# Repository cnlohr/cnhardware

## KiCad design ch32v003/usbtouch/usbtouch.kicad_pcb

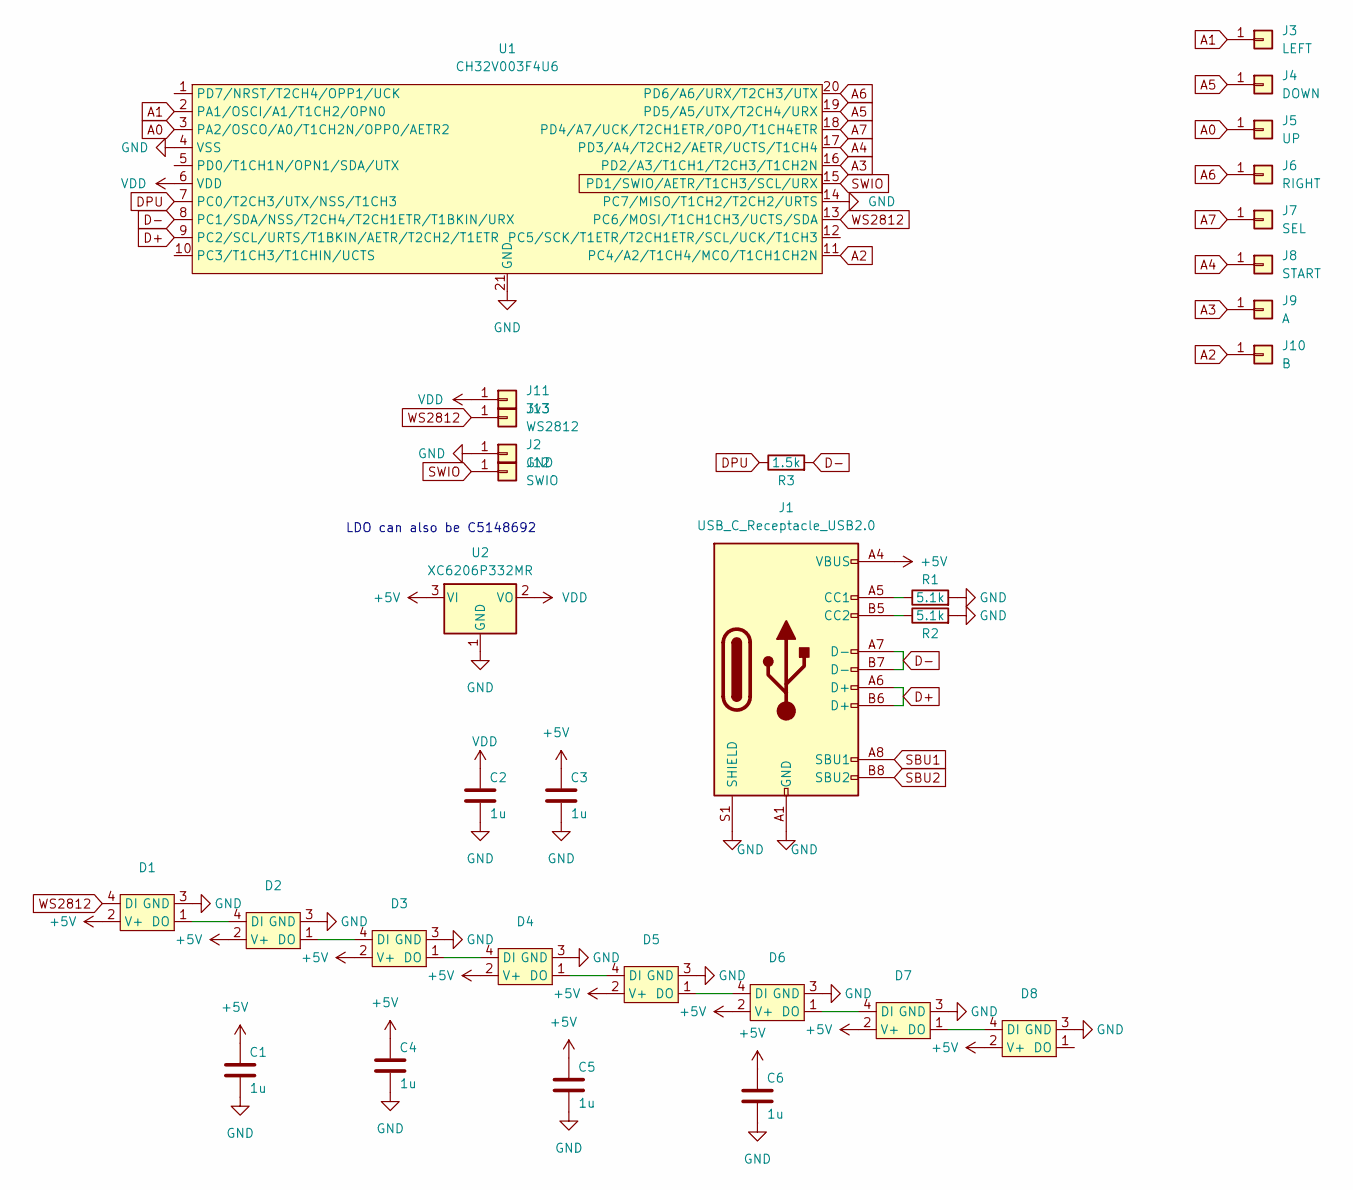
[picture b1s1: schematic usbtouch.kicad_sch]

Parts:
C1, C2, C3, C4, C5, C6: 1u; C_0603_1608Metric; LCSC C15849
D1, D2, D3, D4, D5, D6, D7, D8: XL-1615RGBC-WS2812B; LCSC C5349954
J1: USB_C_Receptacle_USB2.0; USB_C_PADDLE; LCSC C2765186
J2: GND; PinHeader_1x01_P2.54mm_Vertical
J3: LEFT; DPAD
J4: DOWN; DPAD
J5: UP; DPAD
J6: RIGHT; DPAD
J7: SEL; STARTSEL
J8: START; STARTSEL
J9: A; AB
J10: B; AB
J11: 3v3; PinHeader_1x01_P2.54mm_Vertical
J12: SWIO; PinHeader_1x01_P2.54mm_Vertical
J13: WS2812; PinHeader_1x01_P2.54mm_Vertical
R1, R2: 5.1k; R_0603_1608Metric; LCSC C23186
R3: 1.5k; R_0603_1608Metric; LCSC C22843
U1: CH32V003F4U6; QFN-20-1EP_3x3mm_P0.4mm_EP1.65x1.65mm; LCSC C5299908
U2: XC6206P332MR; SOT-23; LCSC C5446

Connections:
+5V: C1.2, C3.2, C4.2, C5.2, C6.2, D1.2 (V+), D2.2 (V+), D3.2 (V+), D4.2 (V+), D5.2 (V+), D6.2 (V+), D7.2 (V+), D8.2 (V+), J1.A4 (VBUS), J1.A9 (VBUS), J1.B4 (VBUS), J1.B9 (VBUS), U2.3 (VI)
A0: J5.1, U1.3 (PA2/OSCO/A0/T1CH2N/OPP0/AETR2)
A1: J3.1, U1.2 (PA1/OSCI/A1/T1CH2/OPN0)
A2: J10.1, U1.11 (PC4/A2/T1CH4/MCO/T1CH1CH2N)
A3: J9.1, U1.16 (PD2/A3/T1CH1/T2CH3/T1CH2N)
A4: J8.1, U1.17 (PD3/A4/T2CH2/AETR/UCTS/T1CH4)
A5: J4.1, U1.19 (PD5/A5/UTX/T2CH4/URX)
A6: J6.1, U1.20 (PD6/A6/URX/T2CH3/UTX)
A7: J7.1, U1.18 (PD4/A7/UCK/T2CH1ETR/OPO/T1CH4ETR)
D+: J1.A6 (D+), J1.B6 (D+), U1.9 (PC2/SCL/URTS/T1BKIN/AETR/T2CH2/T1ETR)
D-: J1.A7 (D-), J1.B7 (D-), R3.2, U1.8 (PC1/SDA/NSS/T2CH4/T2CH1ETR/T1BKIN/URX)
DPU: R3.1, U1.7 (PC0/T2CH3/UTX/NSS/T1CH3)
GND: C1.1, C2.1, C3.1, C4.1, C5.1, C6.1, D1.3 (GND), D2.3 (GND), D3.3 (GND), D4.3 (GND), D5.3 (GND), D6.3 (GND), D7.3 (GND), D8.3 (GND), J1.A1 (GND), J1.A12 (GND), J1.B1 (GND), J1.B12 (GND), J1.S1 (SHIELD), J2.1, R1.2, R2.2, U1.4 (VSS), U1.14 (PC7/MISO/T1CH2/T2CH2/URTS), U1.21 (GND), U2.1 (GND)
unnamed: D1.1 (DO), D2.4 (DI)
unnamed: D2.1 (DO), D3.4 (DI)
unnamed: D3.1 (DO), D4.4 (DI)
unnamed: D4.1 (DO), D5.4 (DI)
unnamed: D5.1 (DO), D6.4 (DI)
unnamed: D6.1 (DO), D7.4 (DI)
unnamed: D7.1 (DO), D8.4 (DI)
unnamed: J1.A5 (CC1), R1.1
unnamed: J1.B5 (CC2), R2.1
SBU1: J1.A8 (SBU1)
SBU2: J1.B8 (SBU2)
SWIO: J12.1, U1.15 (PD1/SWIO/AETR/T1CH3/SCL/URX)
VDD: C2.2, J11.1, U1.6 (VDD), U2.2 (VO)
WS2812: D1.4 (DI), J13.1, U1.13 (PC6/MOSI/T1CH1CH3/UCTS/SDA)

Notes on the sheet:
LDO can also be C5148692

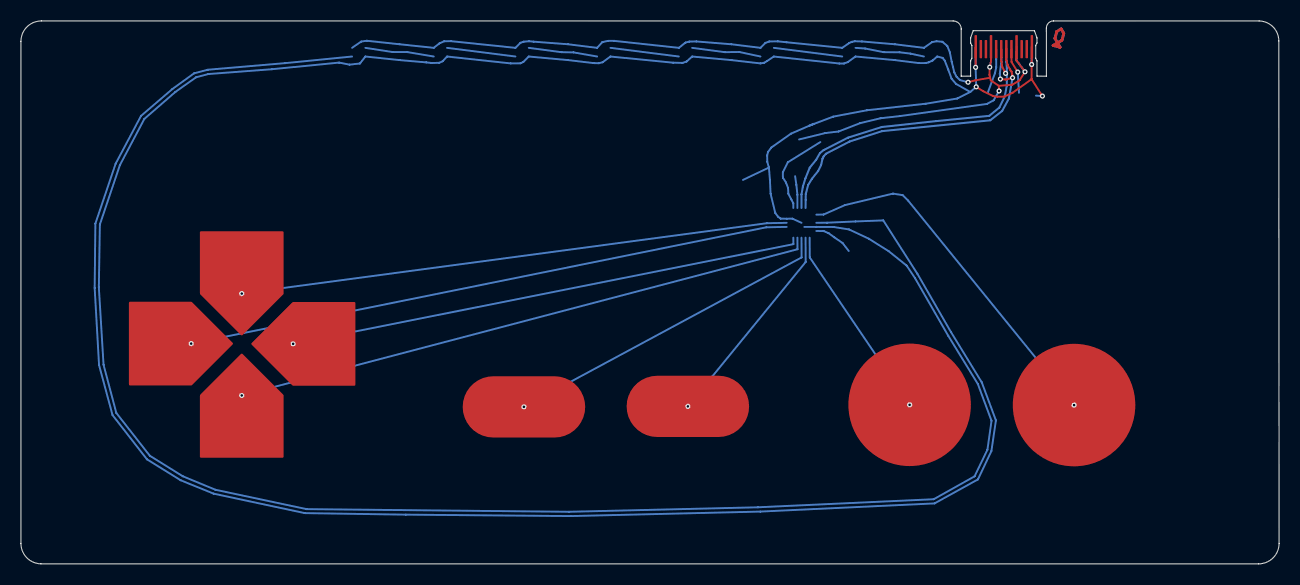
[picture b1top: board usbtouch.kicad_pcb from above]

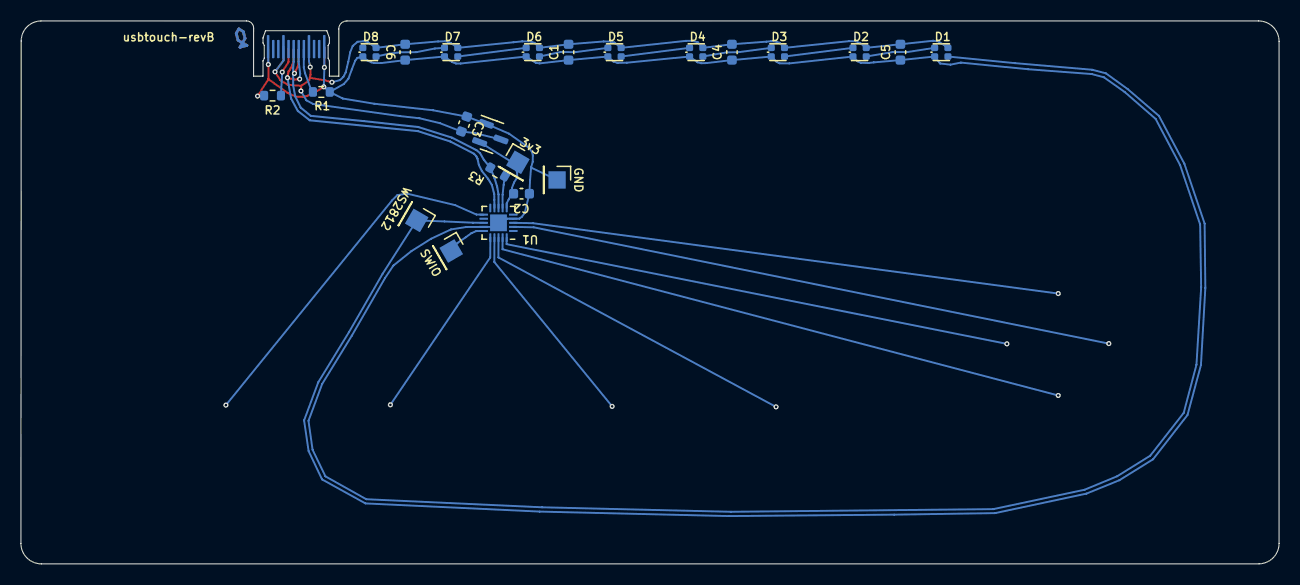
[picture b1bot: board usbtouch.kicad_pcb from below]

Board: 2 copper layers, 123.2 x 53.2 mm, 32 parts (24 on the bottom side), 25 nets.

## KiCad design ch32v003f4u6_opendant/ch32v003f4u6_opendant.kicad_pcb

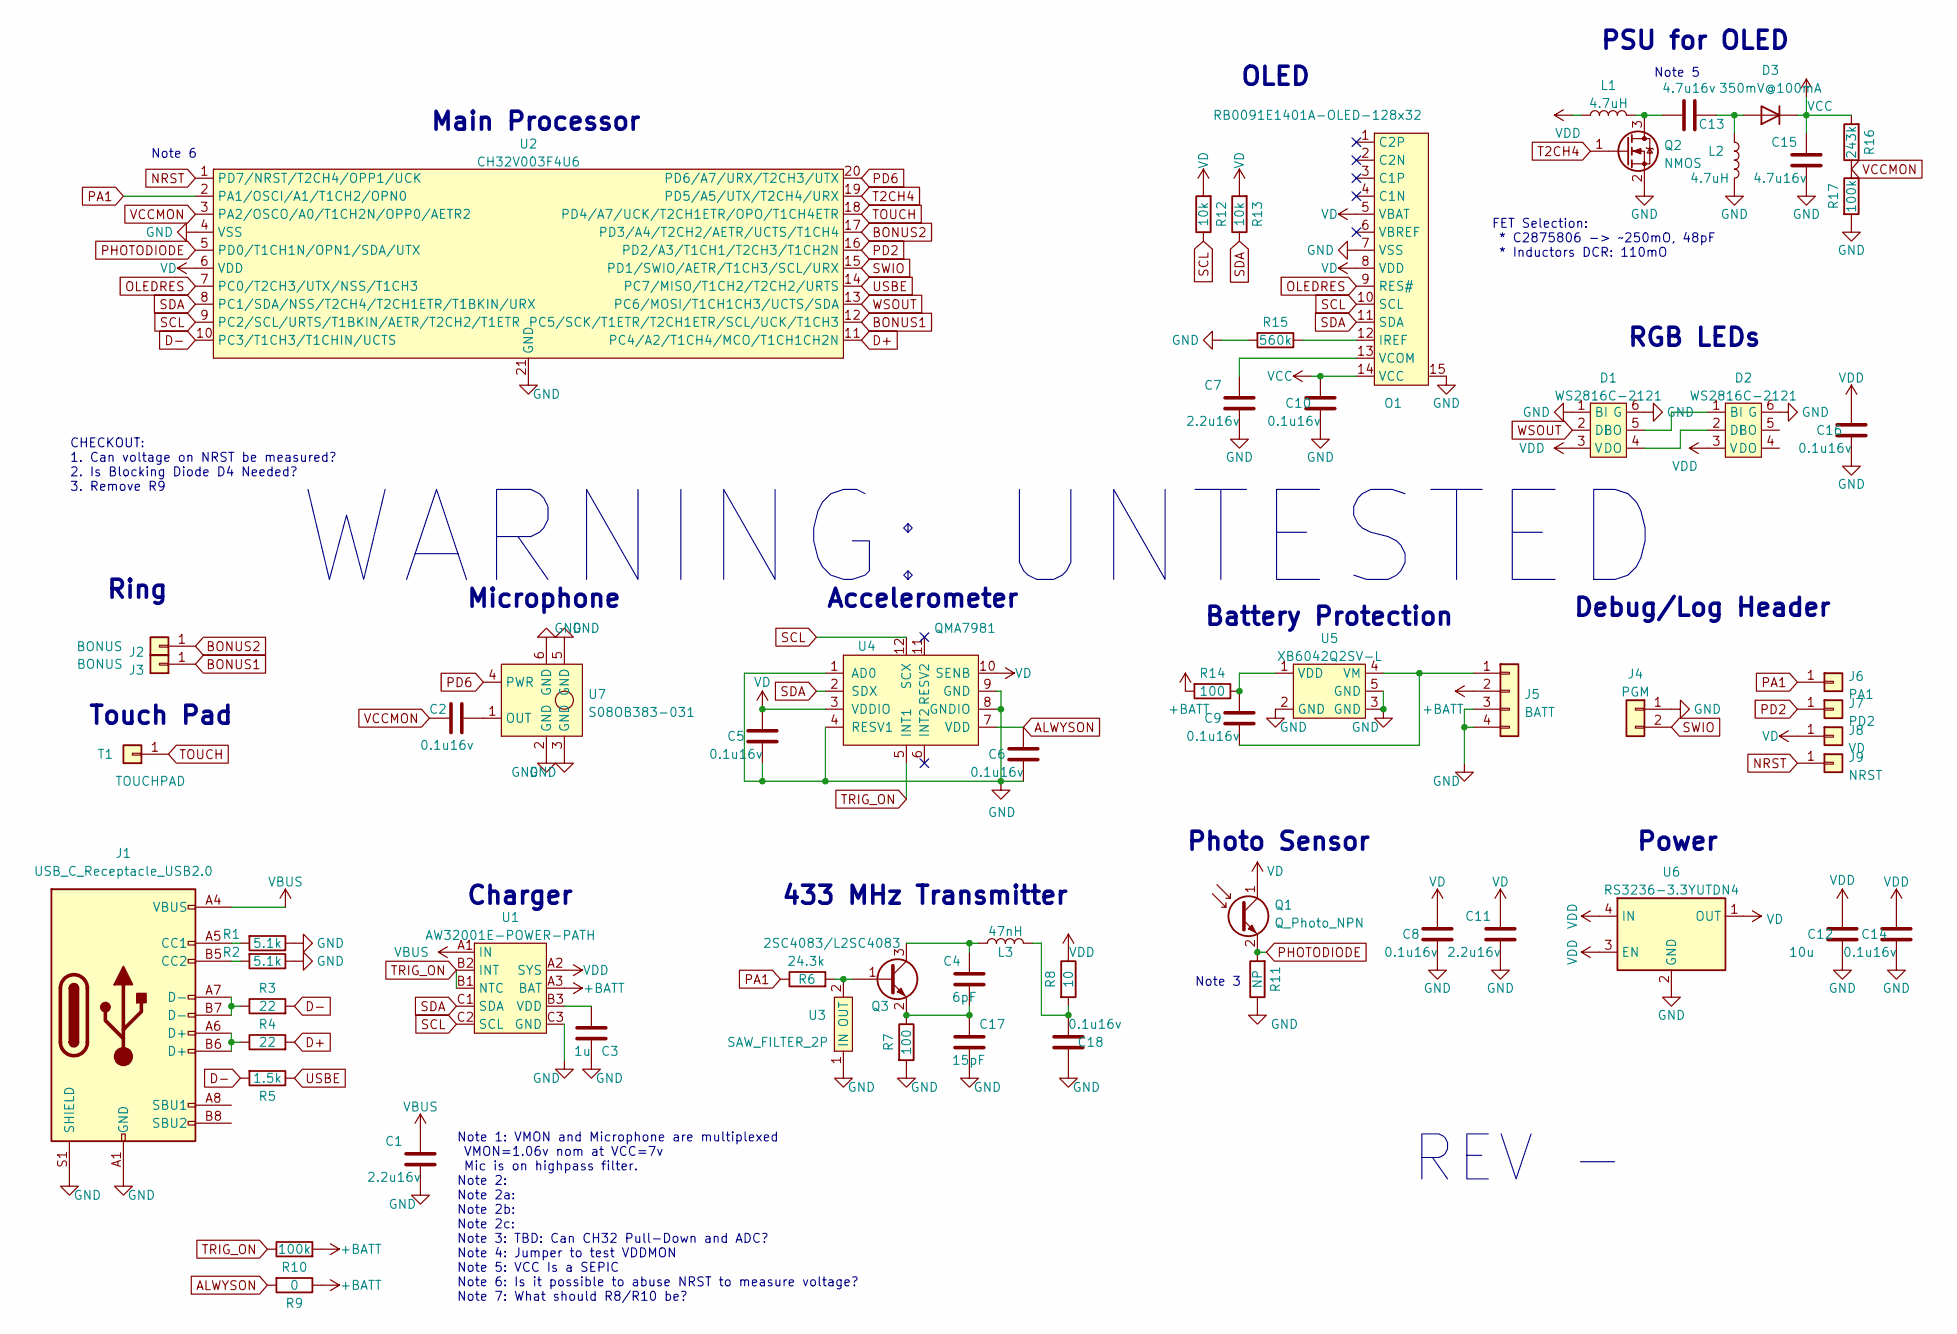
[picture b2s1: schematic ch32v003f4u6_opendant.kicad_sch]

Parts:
C1, C7, C11: 2.2u16v; C_0402_1005Metric; LCSC C385032
C2, C5, C6, C8, C9, C10, C14, C16, C18: 0.1u16v; C_0402_1005Metric; LCSC C338032
C3: 1u; C_0402_1005Metric; LCSC C52923
C4: 6pF; C_0402_1005Metric; LCSC C1575
C12: 10u; C_0402_1005Metric; LCSC C315248
C13, C15: 4.7u16v; C_0402_1005Metric; LCSC C412302
C17: 15pF; C_0402_1005Metric; LCSC C1548
D1, D2: WS2816C-2121; WS2816-2121; LCSC C965561
D3: 350mV@100mA; DFN1006; LCSC C239808
J1: USB_C_Receptacle_USB2.0; USB_C_Receptacle_HRO_TYPE-C-31-M-12; LCSC C2765186
J2, J3: BONUS; MountingHole_2.2mm_M2_DIN965_Pad
J4: PGM; PinHeader_1x02_P2.54mm_Vertical
J5: BATT; SOUHAN-Battery-1.25mm-SMT; LCSC C393945
J6: PA1; GeneralPad-Round-1.5mm
J7: PD2; GeneralPad-Round-1.5mm
J8: VD; GeneralPad-Round-1.5mm
J9: NRST; GeneralPad-Round-1.5mm
L1, L2: 4.7uH; L_0805_2012Metric; LCSC C379996
L3: 47nH; L_0603_1608Metric; LCSC C155023
O1: RB0091E1401A-OLED-128x32; RB0091E1401A-OLED-128x32_FLIP
Q1: Q_Photo_NPN; D_0805_2012Metric; LCSC C100090
Q2: NMOS; DFN-3L-1x0.6; LCSC C2875806
Q3: 2SC4083/L2SC4083; SOT-323_SC-70; LCSC C12064
R1, R2: 5.1k; R_0402_1005Metric; LCSC C114759
R3, R4: 22; R_0402_1005Metric; LCSC C102905
R5: 1.5k; R_0402_1005Metric; LCSC C114759
R6: 24.3k; R_0402_1005Metric; LCSC C226370
R7: 100; R_0402_1005Metric; LCSC C25076
R8: 10; R_0402_1005Metric; LCSC C140210
R9: 0; R_0402_1005Metric; LCSC C17168
R10, R17: 100k; R_0402_1005Metric; LCSC C279979
R11: NP; R_0402_1005Metric
R12, R13: 10k; R_0402_1005Metric; LCSC C269674
R14: 100; R_0402_1005Metric; LCSC C106232
R15: 560k; R_0402_1005Metric; LCSC C137958
R16: 243k; R_0402_1005Metric; LCSC C43249
T1: TOUCHPAD; touchpad_10x6.5mm_retircle
U1: AW32001E-POWER-PATH; BGA-9_1.6x1.6mm_Layout3x3_P0.5mm; LCSC C5125890
U2: CH32V003F4U6; QFN-20-1EP_3x3mm_P0.4mm_EP1.65x1.65mm; LCSC C5299908
U3: SAW_FILTER_2P; SAW-SMD2016-2P; LCSC C2847068
U4: QMA7981; QMA6981; LCSC C457290
U5: XB6042Q2SV-L; xdfn-reg; LCSC C2759995
U6: RS3236-3.3YUTDN4; xdfn-reg; LCSC C379350
U7: S08OB383-031; GOERTEK-S08OB383-031-MemsMic; LCSC S08OB383-031

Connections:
+BATT: J5.2, R9.1, R10.2, R14.2, U1.A3 (BAT)
ALWYSON: C6.1, R9.2, U4.7 (VDD)
BONUS1: J3.1, U2.12 (PC5/SCK/T1ETR/T2CH1ETR/SCL/UCK/T1CH3)
BONUS2: J2.1, U2.17 (PD3/A4/T2CH2/AETR/UCTS/T1CH4)
D+: R4.2, U2.11 (PC4/A2/T1CH4/MCO/T1CH1CH2N)
D-: R3.2, R5.2, U2.10 (PC3/T1CH3/T1CHIN/UCTS)
GND: C1.2, C3.2, C5.2, C6.2, C7.2, C8.2, C10.2, C11.2, C12.2, C14.2, C15.2, C16.2, C17.2, C18.1, D1.1 (BI), D1.6 (G), D2.6 (G), J1.A1 (GND), J1.A12 (GND), J1.B1 (GND), J1.B12 (GND), J1.S1 (SHIELD), J4.1, J5.3, J5.4, L2.2, O1.7 (VSS), O1.15, Q2.2 (S), R1.1, R2.1, R7.2, R11.1, R15.2, R17.2, U1.C3 (GND), U2.4 (VSS), U2.21 (GND), U3.1 (IN), U4.1 (AD0), U4.4 (RESV1), U4.8 (GNDIO), U4.9 (GND), U5.2 (GND), U5.3 (GND), U5.5 (GND), U6.2 (GND), U6.5 (GND), U7.2 (GND), U7.3 (GND), U7.5 (GND), U7.6 (GND)
NRST: J9.1, U2.1 (PD7/NRST/T2CH4/OPP1/UCK)
unnamed: C2.2, U7.1 (OUT)
unnamed: C3.1, U1.B3 (VDD)
unnamed: C4.1, L3.1, Q3.3 (C)
unnamed: C7.1, O1.13 (VCOM)
unnamed: C9.1, R14.1, U5.1 (VDD)
unnamed: C9.2, J5.1, U5.4 (VM)
unnamed: C13.1, L1.2, Q2.3 (D)
unnamed: C13.2, D3.2 (A), L2.1
unnamed: C4.2, C17.1, Q3.2 (E), R7.1
unnamed: C18.2, L3.2, R8.2
unnamed: D1.4 (DO), D2.2 (DI)
unnamed: D1.5 (BO), D2.1 (BI)
unnamed: J1.A5 (CC1), R1.2
unnamed: J1.A6 (D+), J1.B6 (D+), R4.1
unnamed: J1.A7 (D-), J1.B7 (D-), R3.1
unnamed: J1.B5 (CC2), R2.2
unnamed: O1.12 (IREF), R15.1
unnamed: Q3.1 (B), R6.2, U3.2 (OUT)
OLEDRES: O1.9 (RES#), U2.7 (PC0/T2CH3/UTX/NSS/T1CH3)
PA1: J6.1, R6.1, U2.2 (PA1/OSCI/A1/T1CH2/OPN0)
PD2: J7.1, U2.16 (PD2/A3/T1CH1/T2CH3/T1CH2N)
PD6: U2.20 (PD6/A7/URX/T2CH3/UTX), U7.4 (PWR)
PHOTODIODE: Q1.2 (E), R11.2, U2.5 (PD0/T1CH1N/OPN1/SDA/UTX)
SCL: O1.10 (SCL), R12.1, U1.C2 (SCL), U2.9 (PC2/SCL/URTS/T1BKIN/AETR/T2CH2/T1ETR), U4.12 (SCX)
SDA: O1.11 (SDA), R13.1, U1.C1 (SDA), U2.8 (PC1/SDA/NSS/T2CH4/T2CH1ETR/T1BKIN/URX), U4.2 (SDX)
SWIO: J4.2, U2.15 (PD1/SWIO/AETR/T1CH3/SCL/URX)
T2CH4: Q2.1 (G), U2.19 (PD5/A5/UTX/T2CH4/URX)
TOUCH: T1.1, U2.18 (PD4/A7/UCK/T2CH1ETR/OPO/T1CH4ETR)
TRIG_ON: R10.1, U1.B1 (NTC), U1.B2 (INT), U4.5 (INT1)
USBE: R5.1, U2.14 (PC7/MISO/T1CH2/T2CH2/URTS)
VBUS: C1.1, J1.A4 (VBUS), J1.A9 (VBUS), J1.B4 (VBUS), J1.B9 (VBUS), U1.A1 (IN)
VCC: C10.1, C15.1, D3.1 (K), O1.14 (VCC), R16.2
VCCMON: C2.1, R16.1, R17.1, U2.3 (PA2/OSCO/A0/T1CH2N/OPP0/AETR2)
VD: C5.1, C8.1, C11.1, J8.1, O1.5 (VBAT), O1.8 (VDD), Q1.1 (C), R12.2, R13.2, U2.6 (VDD), U4.3 (VDDIO), U4.10 (SENB), U6.1 (OUT)
VDD: C12.1, C14.1, C16.1, D1.3 (V), D2.3 (V), L1.1, R8.1, U1.A2 (SYS), U6.3 (EN), U6.4 (IN)
WSOUT: D1.2 (DI), U2.13 (PC6/MOSI/T1CH1CH3/UCTS/SDA)

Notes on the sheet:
Accelerometer
Note 5
REV -
Ring
Microphone
Note 3
WARNING: UNTESTED
433 MHz Transmitter
RGB LEDs
Battery Protection
PSU for OLED
Debug/Log Header
OLED
FET Selection: * C2875806 -> ~250mO, 48pF * Inductors DCR: 110mO
Main Processor
Power
Charger
Photo Sensor
Note 6
CHECKOUT: 1. Can voltage on NRST be measured? 2. Is Blocking Diode D4 Needed? 3. Remove R9
Note 1: VMON and Microphone are multiplexed VMON=1.06v nom at VCC=7v Mic is on highpass filter. Note 2: Note 2a: Note 2b: Note 2c: Note 3: TBD: Can CH32 Pull-Down and ADC? Note 4: Jumper to test VDDMON Note 5: VCC Is a SEPIC Note 6: Is it possible to abuse NRST to measure voltage? Note 7: What shou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
Touch Pad

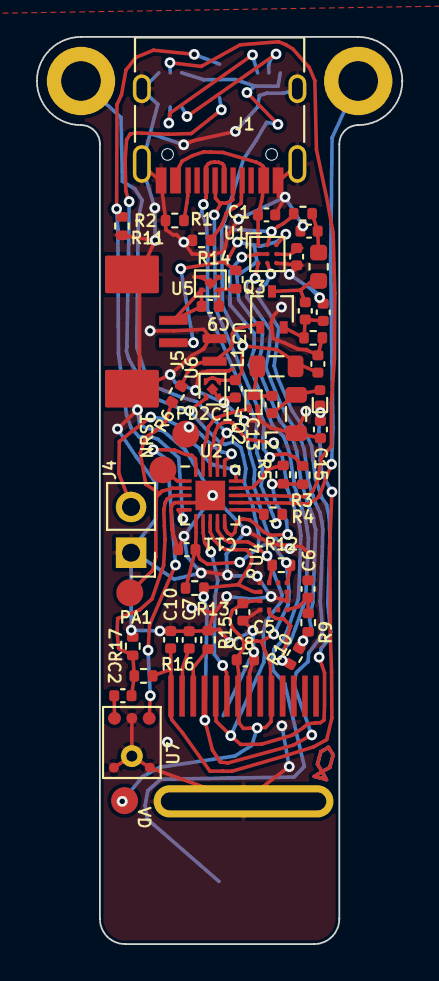
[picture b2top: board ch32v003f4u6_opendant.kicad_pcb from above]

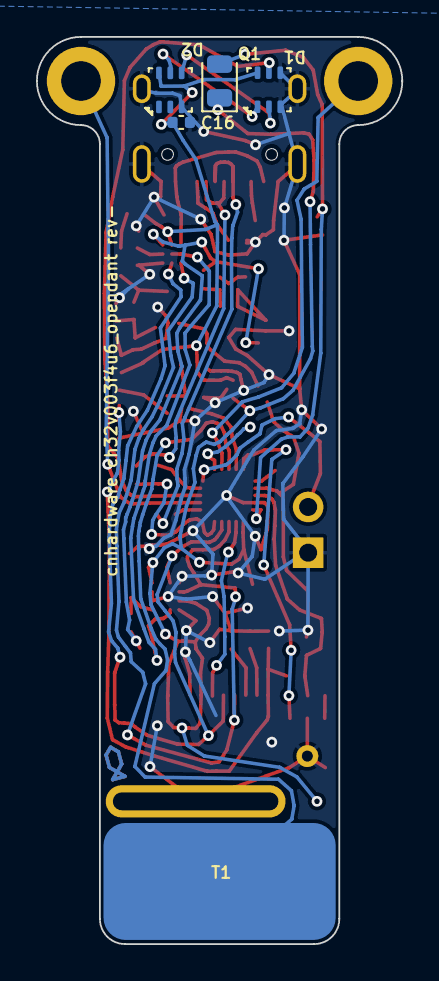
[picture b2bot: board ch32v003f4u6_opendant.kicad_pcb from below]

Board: 2 copper layers, 20.3 x 50.4 mm, 62 parts (5 on the bottom side), 44 nets.

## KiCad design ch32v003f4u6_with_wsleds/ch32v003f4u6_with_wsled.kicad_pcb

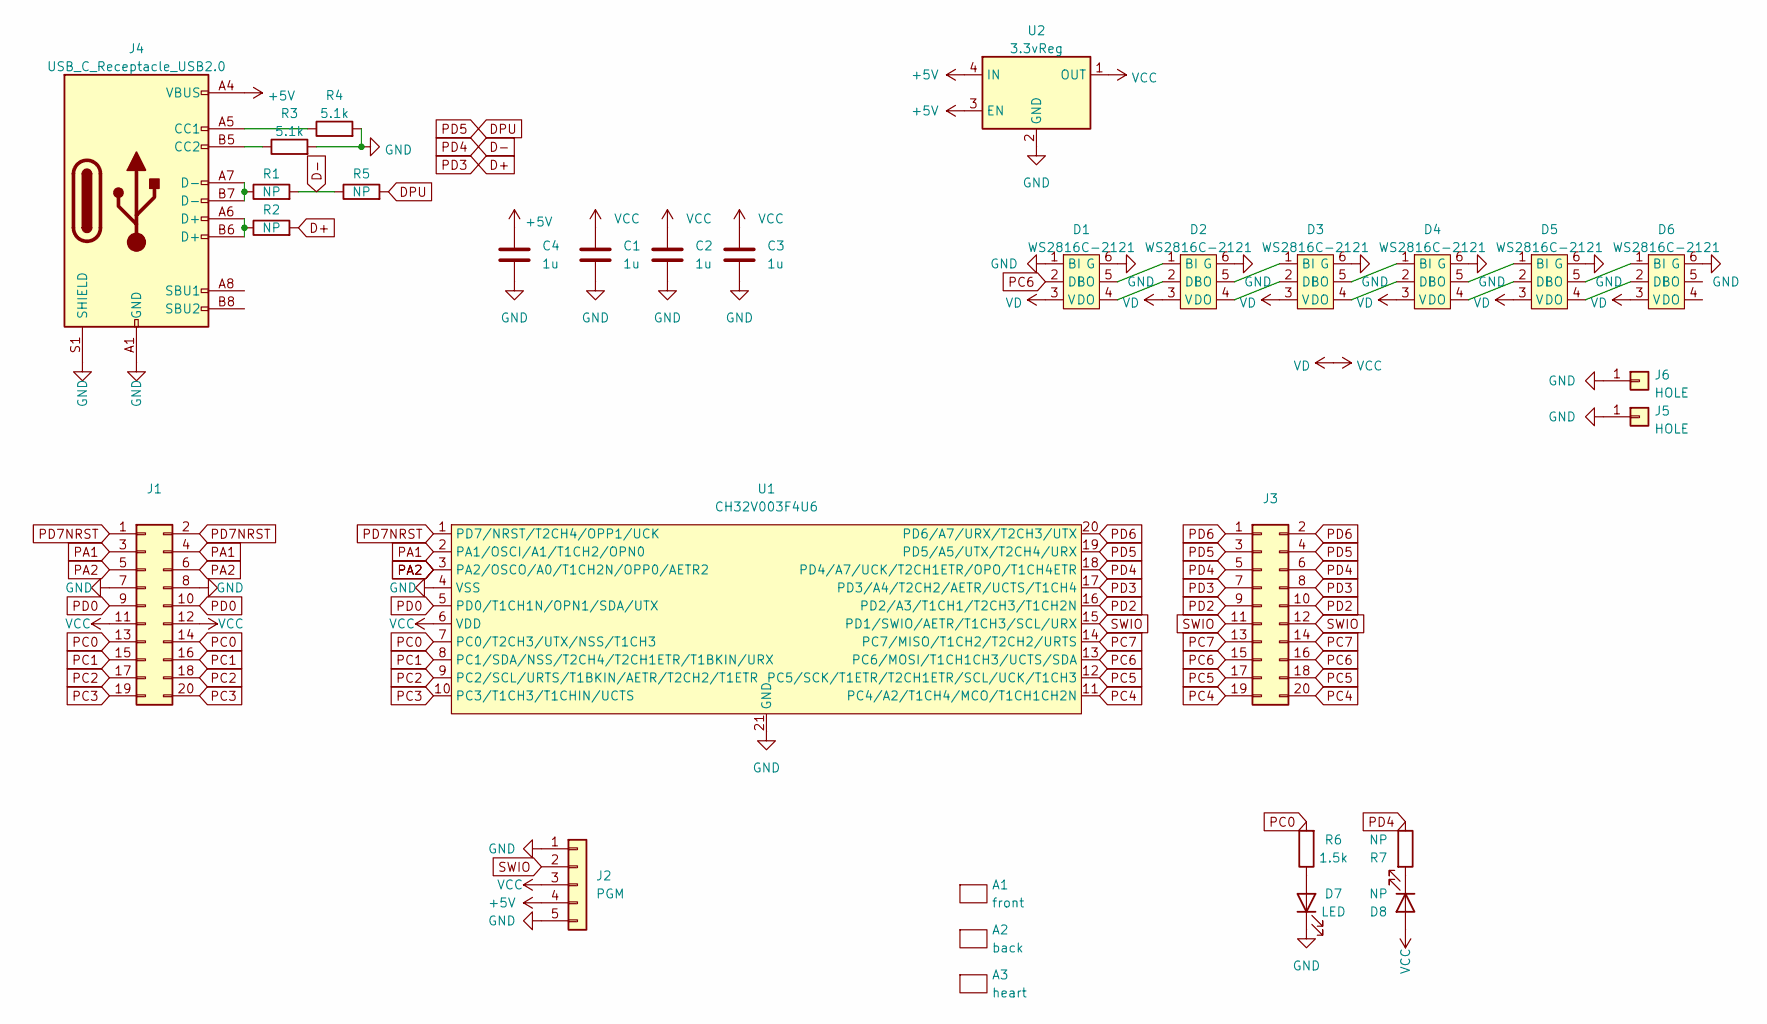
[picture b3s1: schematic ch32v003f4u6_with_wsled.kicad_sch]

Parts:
A1: front; Front
A2: back; Back
A3: heart; Heart
C1, C2, C3, C4: 1u; C_0402_1005Metric; LCSC C237173
D1, D2, D3, D4, D5, D6: WS2816C-2121; WS2816-2121; LCSC C965561
D7: LED; LED_0402_1005Metric; LCSC C74342
D8: NP; LED_0402_1005Metric; LCSC NP
J1, J3: PinHeader_2x10_P2.54mm_Vertical; LCSC C124359
J2: PGM; PinHeader_1x05_P2.54mm_Vertical; LCSC C358687
J4: USB_C_Receptacle_USB2.0; USB_C_Receptacle_HRO_TYPE-C-31-M-12; LCSC C709358
J5, J6: HOLE; MountingHole_2.2mm_M2_DIN965_Pad
R1, R2, R5: NP; R_0402_1005Metric
R3, R4: 5.1k; R_0402_1005Metric; LCSC C258132
R6: 1.5k; R_0402_1005Metric; LCSC C25867
R7: NP; R_0402_1005Metric; LCSC NP
U1: CH32V003F4U6; QFN-20-1EP_3x3mm_P0.4mm_EP1.65x1.65mm; LCSC C5299908
U2: 3.3vReg; xdfn-reg; LCSC C81114

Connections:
+5V: C4.1, J2.4, J4.A4 (VBUS), J4.A9 (VBUS), J4.B4 (VBUS), J4.B9 (VBUS), U2.3 (EN), U2.4 (IN)
D+: J3.7, J3.8, R2.2, U1.17 (PD3/A4/T2CH2/AETR/UCTS/T1CH4)
D-: J3.5, J3.6, R1.2, R5.1, R7.1, U1.18 (PD4/A7/UCK/T2CH1ETR/OPO/T1CH4ETR)
DPU: J3.3, J3.4, R5.2, U1.19 (PD5/A5/UTX/T2CH4/URX)
GND: C1.2, C2.2, C3.2, C4.2, D1.1 (BI), D1.6 (G), D2.6 (G), D3.6 (G), D4.6 (G), D5.6 (G), D6.6 (G), D7.1 (K), J1.7, J1.8, J2.1, J2.5, J4.A1 (GND), J4.A12 (GND), J4.B1 (GND), J4.B12 (GND), J4.S1 (SHIELD), J5.1, J6.1, R3.2, R4.2, U1.4 (VSS), U1.21 (GND), U2.2 (GND), U2.5 (GND)
unnamed: D1.4 (DO), D2.2 (DI)
unnamed: D1.5 (BO), D2.1 (BI)
unnamed: D2.4 (DO), D3.2 (DI)
unnamed: D2.5 (BO), D3.1 (BI)
unnamed: D3.4 (DO), D4.2 (DI)
unnamed: D3.5 (BO), D4.1 (BI)
unnamed: D4.4 (DO), D5.2 (DI)
unnamed: D4.5 (BO), D5.1 (BI)
unnamed: D5.4 (DO), D6.2 (DI)
unnamed: D5.5 (BO), D6.1 (BI)
unnamed: D7.2 (A), R6.1
unnamed: D8.1 (K), R7.2
unnamed: J4.A5 (CC1), R4.1
unnamed: J4.A6 (D+), J4.B6 (D+), R2.1
unnamed: J4.A7 (D-), J4.B7 (D-), R1.1
unnamed: J4.B5 (CC2), R3.1
PA1: J1.3, J1.4, U1.2 (PA1/OSCI/A1/T1CH2/OPN0)
PA2: J1.5, J1.6, U1.3 (PA2/OSCO/A0/T1CH2N/OPP0/AETR2)
PC0: J1.13, J1.14, R6.2, U1.7 (PC0/T2CH3/UTX/NSS/T1CH3)
PC1: J1.15, J1.16, U1.8 (PC1/SDA/NSS/T2CH4/T2CH1ETR/T1BKIN/URX)
PC2: J1.17, J1.18, U1.9 (PC2/SCL/URTS/T1BKIN/AETR/T2CH2/T1ETR)
PC3: J1.19, J1.20, U1.10 (PC3/T1CH3/T1CHIN/UCTS)
PC4: J3.19, J3.20, U1.11 (PC4/A2/T1CH4/MCO/T1CH1CH2N)
PC5: J3.17, J3.18, U1.12 (PC5/SCK/T1ETR/T2CH1ETR/SCL/UCK/T1CH3)
PC6: D1.2 (DI), J3.15, J3.16, U1.13 (PC6/MOSI/T1CH1CH3/UCTS/SDA)
PC7: J3.13, J3.14, U1.14 (PC7/MISO/T1CH2/T2CH2/URTS)
PD0: J1.9, J1.10, U1.5 (PD0/T1CH1N/OPN1/SDA/UTX)
PD2: J3.9, J3.10, U1.16 (PD2/A3/T1CH1/T2CH3/T1CH2N)
PD6: J3.1, J3.2, U1.20 (PD6/A7/URX/T2CH3/UTX)
PD7NRST: J1.1, J1.2, U1.1 (PD7/NRST/T2CH4/OPP1/UCK)
SWIO: J2.2, J3.11, J3.12, U1.15 (PD1/SWIO/AETR/T1CH3/SCL/URX)
VCC: C1.1, C2.1, C3.1, D1.3 (V), D2.3 (V), D3.3 (V), D4.3 (V), D5.3 (V), D6.3 (V), D8.2 (A), J1.11, J1.12, J2.3, U1.6 (VDD), U2.1 (OUT)

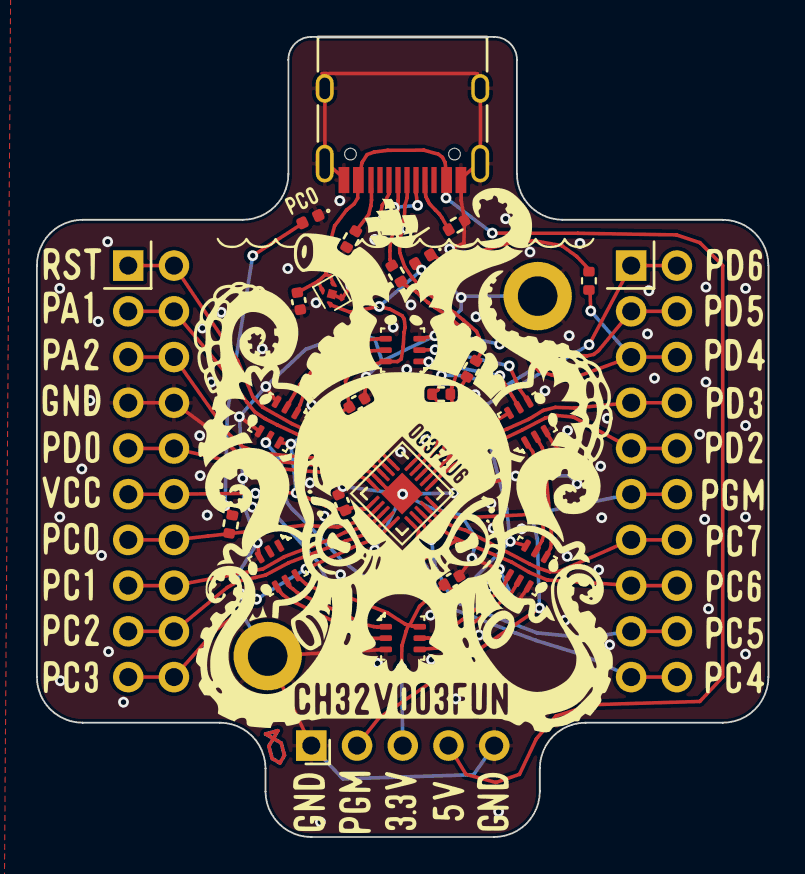
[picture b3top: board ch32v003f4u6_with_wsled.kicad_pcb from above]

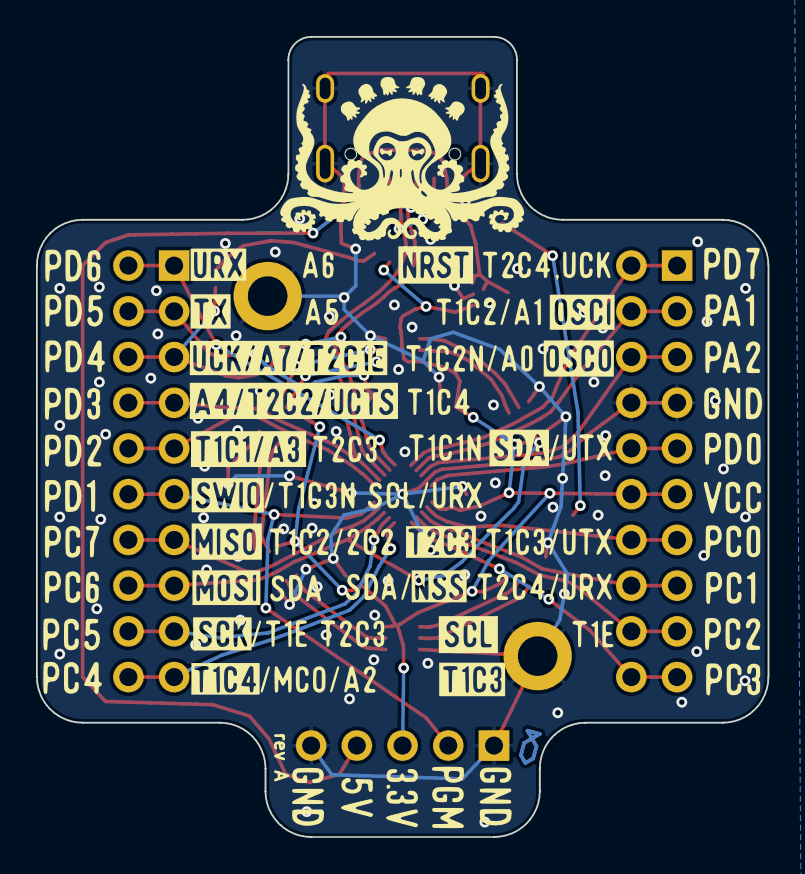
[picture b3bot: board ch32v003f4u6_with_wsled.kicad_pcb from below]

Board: 2 copper layers, 40.6 x 44.5 mm, 30 parts (2 on the bottom side), 37 nets.

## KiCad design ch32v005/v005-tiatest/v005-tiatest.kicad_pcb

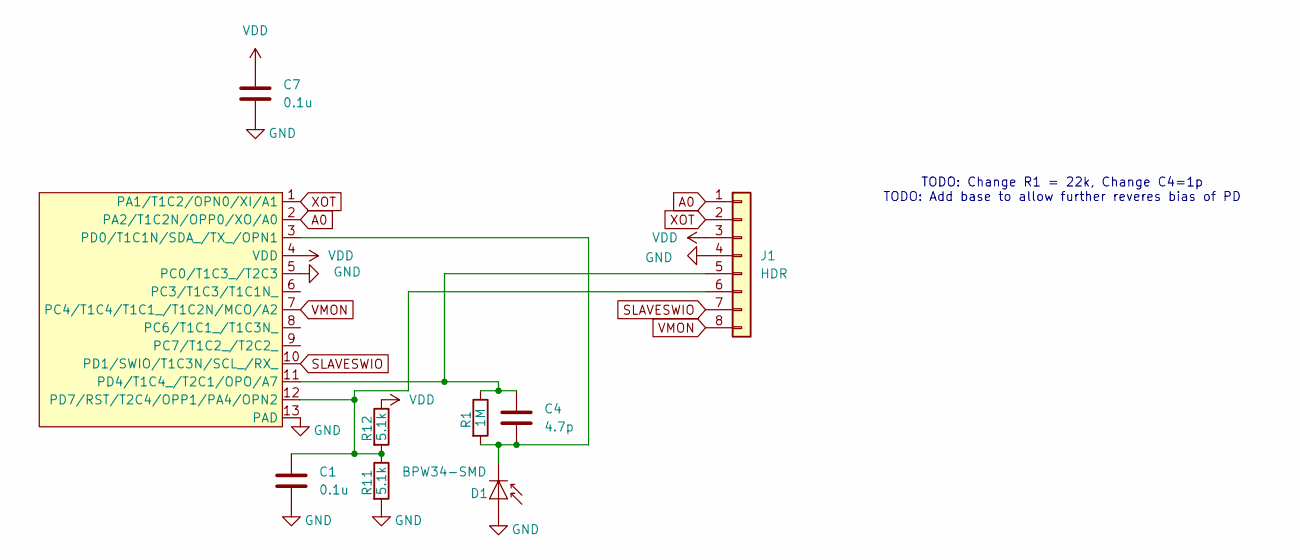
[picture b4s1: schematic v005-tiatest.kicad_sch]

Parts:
C1, C7: 0.1u; C_0402_1005Metric; LCSC C307331
C4: 4.7p; C_0603_1608Metric; LCSC C1634
D1: BPW34-SMD; Osram_BPW34S-SMD; LCSC C145262
J1: HDR; PinHeader_1x08_P2.54mm_Vertical; LCSC C2905487
R1: 1M; R_0603_1608Metric; LCSC C22935
R11, R12: 5.1k; R_0402_1005Metric; LCSC C25905
U3: QFN-12-P0.4-WCH; LCSC C49006243

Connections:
A0: J1.1, U3.2 (PA2/T1C2N/OPP0/XO/A0)
GND: C1.2, C7.2, D1.2 (A), J1.4, R11.2, U3.5 (PC0/T1C3_/T2C3), U3.13 (PAD)
unnamed: C4.1, D1.1 (K), R1.2, U3.3 (PD0/T1C1N/SDA_/TX_/OPN1)
unnamed: C4.2, J1.5, R1.1, U3.11 (PD4/T1C4_/T2C1/OPO/A7)
unnamed: C1.1, J1.6, R11.1, R12.2, U3.12 (PD7/RST/T2C4/OPP1/PA4/OPN2)
SLAVESWIO: J1.7, U3.10 (PD1/SWIO/T1C3N/SCL_/RX_)
VDD: C7.1, J1.3, R12.1, U3.4 (VDD)
VMON: J1.8, U3.7 (PC4/T1C4/T1C1_/T1C2N/MCO/A2)
XOT: J1.2, U3.1 (PA1/T1C2/OPN0/XI/A1)

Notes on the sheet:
TODO: Change R1 = 22k, Change C4=1p TODO: Add base to allow further reveres bias of PD

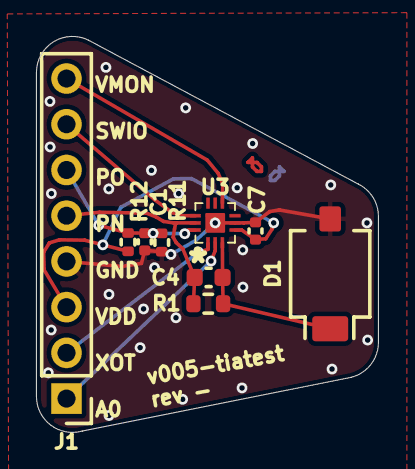
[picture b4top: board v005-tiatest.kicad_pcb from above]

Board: 2 copper layers, 19.0 x 22.0 mm, 9 parts (0 on the bottom side), 9 nets.

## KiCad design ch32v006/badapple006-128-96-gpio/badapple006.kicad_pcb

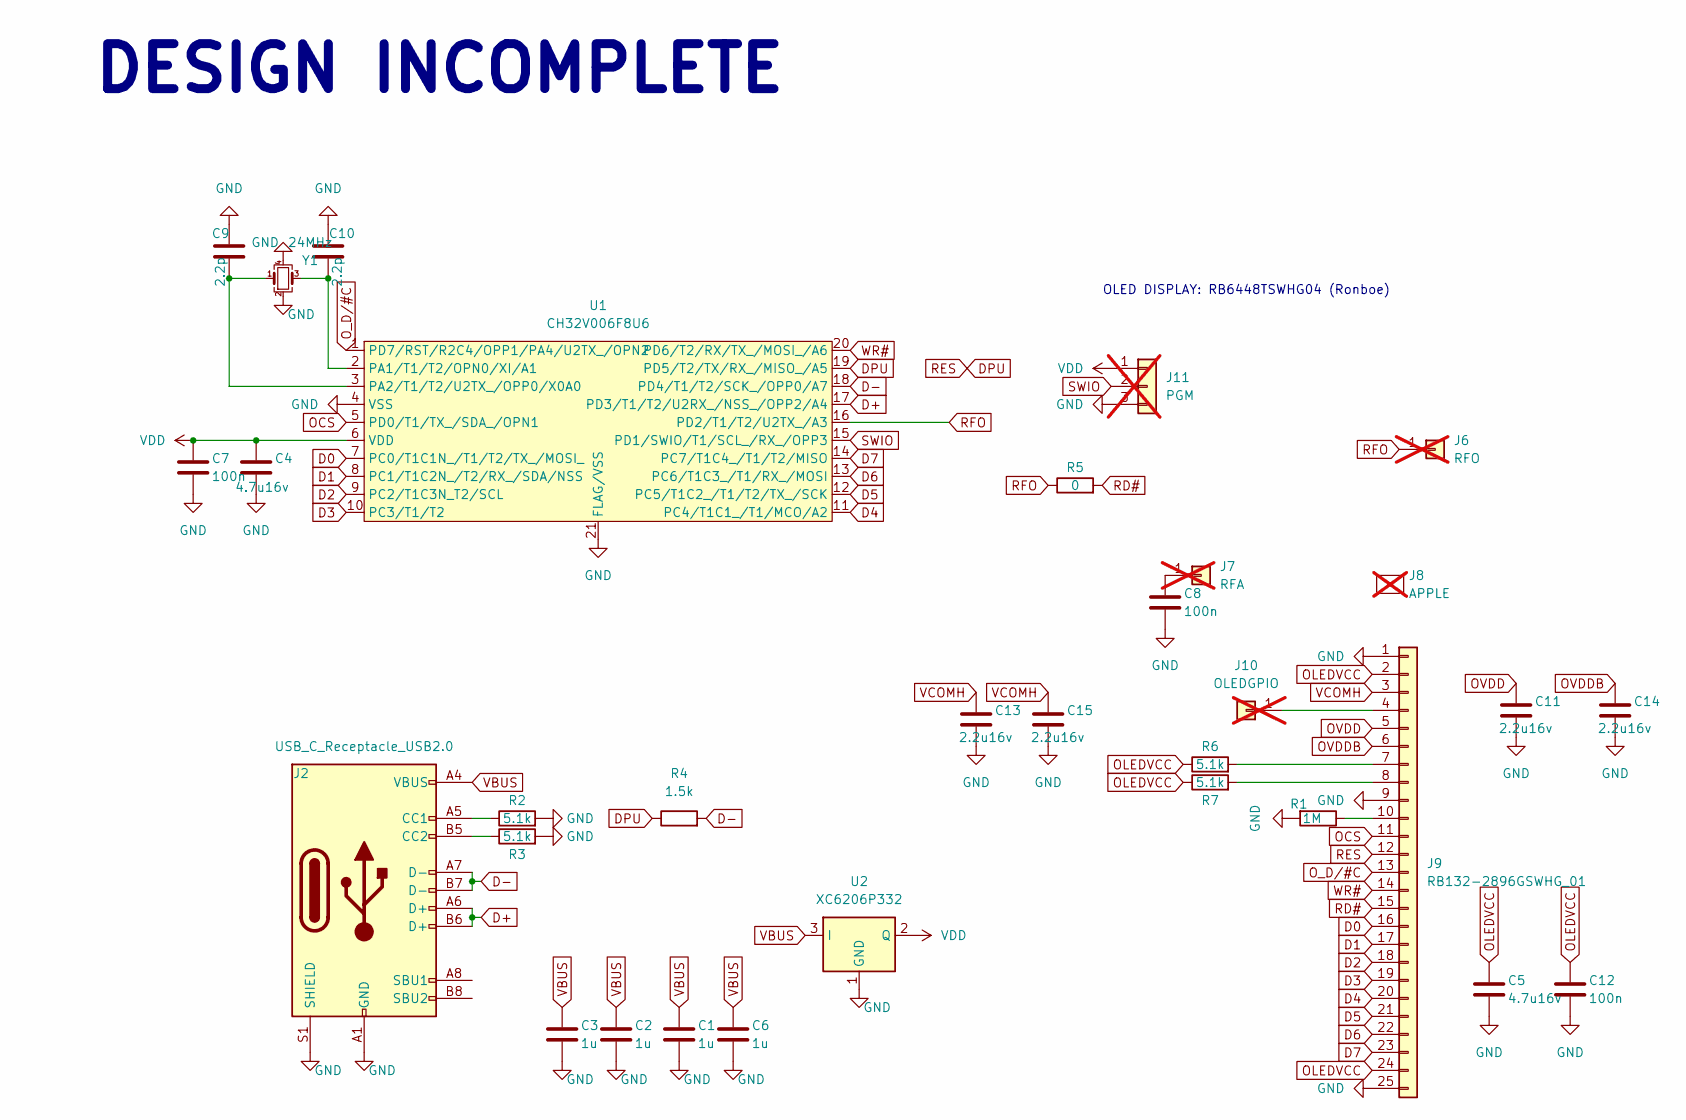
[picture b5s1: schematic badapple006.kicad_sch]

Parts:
C1, C2, C3, C6: 1u; C_0805_2012Metric; LCSC C28323
C4: 4.7u16v; C_0402_1005Metric; LCSC C72203
C5: 4.7u16v; C_0603_1608Metric; LCSC C77045
C7, C8, C12: 100n; C_0402_1005Metric; LCSC C1525
C9, C10: 2.2p; C_0402_1005Metric; LCSC C1559
C11, C13, C14, C15: 2.2u16v; C_0402_1005Metric; LCSC C72203
J2: USB_C_Receptacle_USB2.0; USB_C_PADDLE; LCSC C2765186
J6: RFO; TestPoint_Pad_D1.0mm; not fitted
J7: RFA; TestPoint_Pad_D1.0mm; not fitted
J8: APPLE; apple; not fitted
J9: RB132-2896GSWHG_01
J10: OLEDGPIO; TestPoint_Pad_D1.0mm; not fitted
J11: PGM; PinHeader_1x03_P2.54mm_Vertical; not fitted
R1: 1M; R_0402_1005Metric; LCSC C26083
R2, R3, R6, R7: 5.1k; R_0402_1005Metric; LCSC C105872
R4: 1.5k; R_0402_1005Metric; LCSC C25867
R5: 0; R_0402_1005Metric; LCSC C17168
U1: CH32V006F8U6; QFN-20-1EP_3x3mm_P0.4mm_EP1.65x1.65mm; LCSC C42431288
U2: XC6206P332; SOT-23; LCSC C5446
Y1: 24MHz; Crystal_SMD_2016-4Pin_2.0x1.6mm; LCSC C2929397

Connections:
D0: J9.16, U1.7 (PC0/T1C1N_/T1/T2/TX_/MOSI_)
D1: J9.17, U1.8 (PC1/T1C2N_/T2/RX_/SDA/NSS)
D2: J9.18, U1.9 (PC2/T1C3N_T2/SCL)
D3: J9.19, U1.10 (PC3/T1/T2)
D4: J9.20, U1.11 (PC4/T1C1_/T1/MCO/A2)
D5: J9.21, U1.12 (PC5/T1C2_/T1/T2/TX_/SCK)
D6: J9.22, U1.13 (PC6/T1C3_/T1/RX_/MOSI)
D7: J9.23, U1.14 (PC7/T1C4_/T1/T2/MISO)
D+: J2.A6 (D+), J2.B6 (D+), U1.17 (PD3/T1/T2/U2RX_/NSS_/OPP2/A4)
D-: J2.A7 (D-), J2.B7 (D-), R4.2, U1.18 (PD4/T1/T2/SCK_/OPP0/A7)
DPU: J9.12, R4.1, U1.19 (PD5/T2/TX/RX_/MISO_/A5)
GND: C1.2, C2.2, C3.2, C4.2, C5.2, C6.2, C7.2, C8.2, C9.1, C10.1, C11.2, C12.2, C13.2, C14.2, C15.2, J2.A1 (GND), J2.A12 (GND), J2.B1 (GND), J2.B12 (GND), J2.S1 (SHIELD), J9.1, J9.9, J9.25, J11.3, R1.2, R2.2, R3.2, U1.4 (VSS), U1.21 (FLAG/VSS), U2.1 (GND), Y1.2, Y1.4
unnamed: J2.A5 (CC1), R2.1
unnamed: J2.B5 (CC2), R3.1
unnamed: C8.1, J7.1
unnamed: J9.7, R6.2
unnamed: J9.8, R7.2
unnamed: J9.10, R1.1
unnamed: J9.4, J10.1
unnamed: C10.2, U1.2 (PA1/T1/T2/OPN0/XI/A1), Y1.3
unnamed: C9.2, U1.3 (PA2/T1/T2/U2TX_/OPP0/X0A0), Y1.1
OCS: J9.11, U1.5 (PD0/T1/TX_/SDA_/OPN1)
OLEDVCC: C5.1, C12.1, J9.2, J9.24, R6.1, R7.1
OVDD: C11.1, J9.5
OVDDB: C14.1, J9.6
O_D/#C: J9.13, U1.1 (PD7/RST/R2C4/OPP1/PA4/U2TX_/OPN2)
RD#: J9.15, R5.2
RFO: J6.1, R5.1, U1.16 (PD2/T1/T2/U2TX_/A3)
SWIO: J11.2, U1.15 (PD1/SWIO/T1/SCL_/RX_/OPP3)
VBUS: C1.1, C2.1, C3.1, C6.1, J2.A4 (VBUS), J2.A9 (VBUS), J2.B4 (VBUS), J2.B9 (VBUS), U2.3 (I)
VCOMH: C13.1, C15.1, J9.3
VDD: C4.1, C7.1, J11.1, U1.6 (VDD), U2.2 (Q)
WR#: J9.14, U1.20 (PD6/T2/RX/TX_/MOSI_/A6)

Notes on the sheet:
DESIGN INCOMPLETE
OLED DISPLAY: RB6448TSWHG04 (Ronboe)

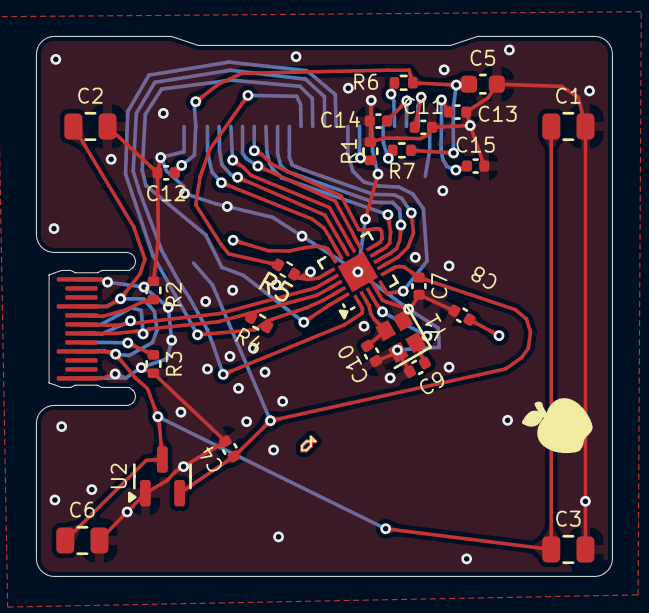
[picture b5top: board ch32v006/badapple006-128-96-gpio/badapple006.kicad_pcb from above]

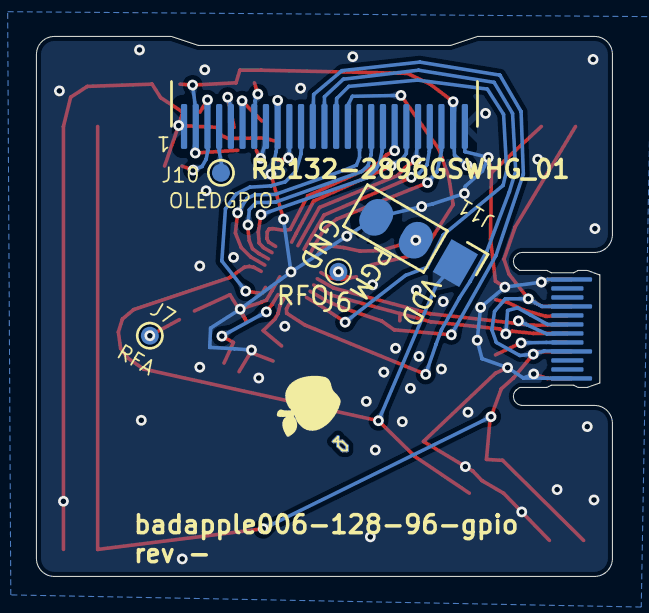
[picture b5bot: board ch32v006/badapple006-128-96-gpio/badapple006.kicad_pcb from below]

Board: 2 copper layers, 32.0 x 30.0 mm, 33 parts (6 on the bottom side), 33 nets.

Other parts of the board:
J8#2: APPLE; apple
